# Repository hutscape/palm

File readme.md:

# Palm

> 🌴 Outdoor BLE-connected UV sensor keychain 🗝

Visit [hutscape.com/palm](https://hutscape.com/palm/) for more details.

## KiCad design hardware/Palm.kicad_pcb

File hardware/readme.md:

# Hardware

## Schematic

View the [schematic](images/schematic.pdf) and [footprint layout](images/footprint.pdf) in PDF format.

## Main components

1. nRF52 Bluefruit Feather Adafruit Breakout board
1. VEML6075 UV Index sensor Adafruit breakout board
1. RGB LED
1. LiPo

## Prototype

## Schematic

## Footprint

Front

Back

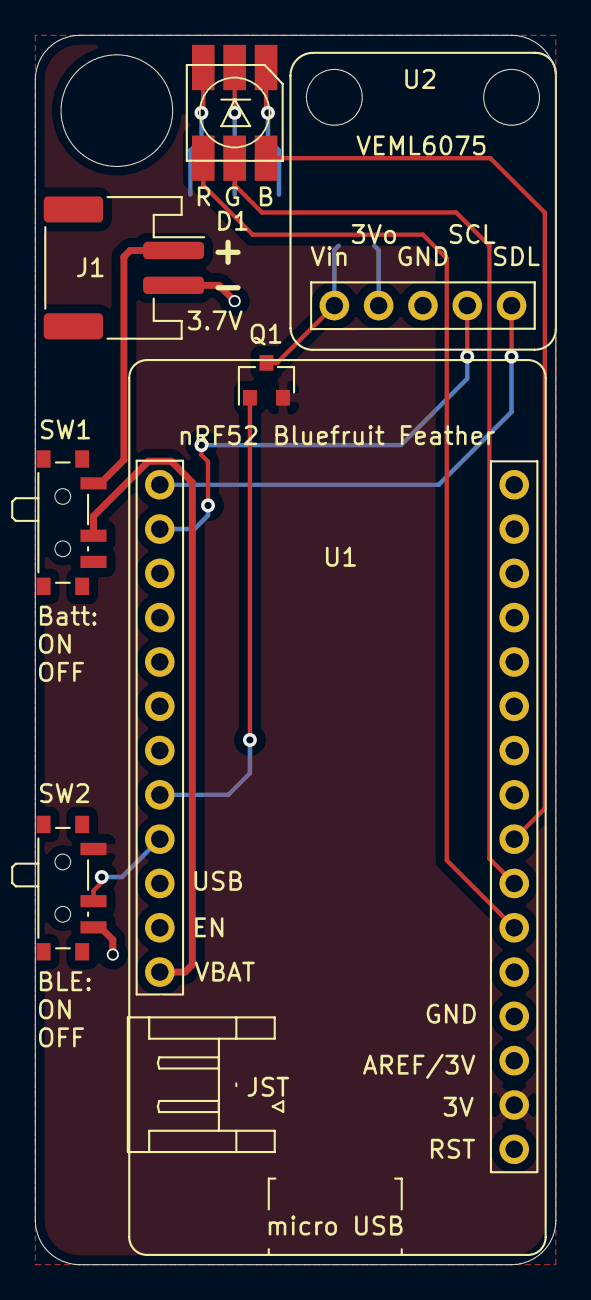
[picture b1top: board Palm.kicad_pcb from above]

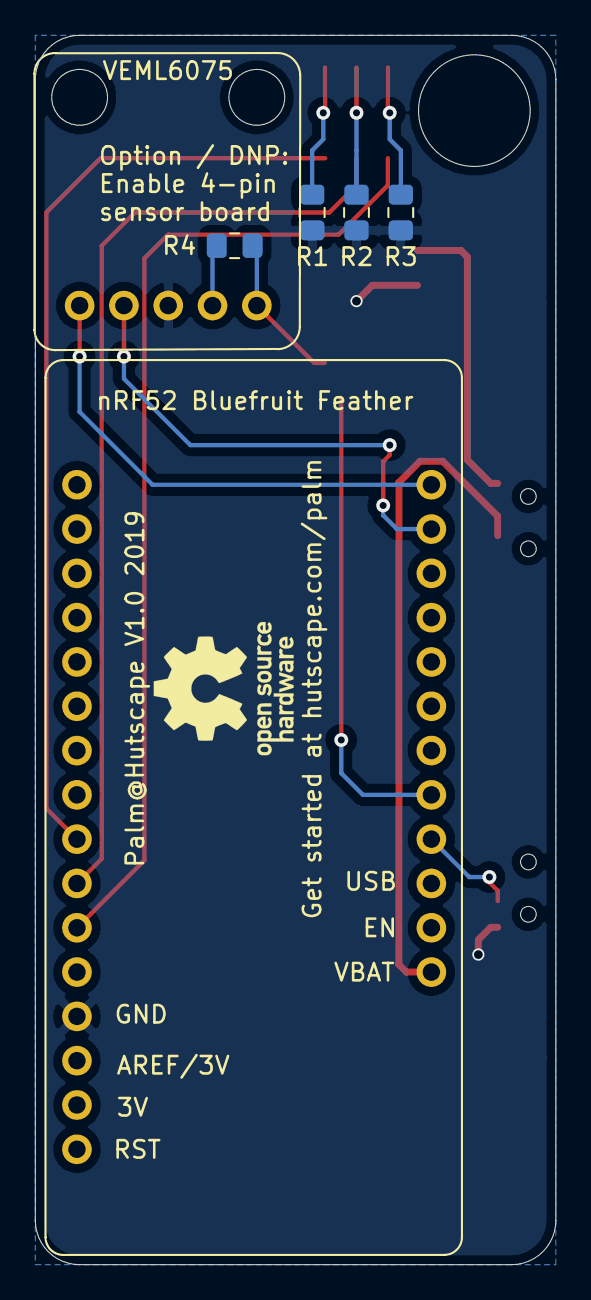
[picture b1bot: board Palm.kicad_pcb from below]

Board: 2 copper layers, 29.8 x 70.5 mm, 11 parts (4 on the bottom side), 16 nets.

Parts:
D1: LED_BARG; LED_RGB_Cree-PLCC-6_5.5x5.5mm_P2.1mm
J1: Conn_01x02_Female; JST_PH_S2B-PH-SM4-TB_1x02-1MP_P2.00mm_Horizontal
Q1: IRLML6402; SOT-23
R1, R2, R3: 1k; R_0805_2012Metric_Pad1.15x1.40mm_HandSolder
R4: 0R; R_0805_2012Metric_Pad1.15x1.40mm_HandSolder
SW1, SW2: SW_SPDT; SW_SPDT_PCM12
U1: Adafruit_nRF52_Feather; nRF52_Bluefruit_Adafruit_breakout_board
U2: VEML6075_breakout; VEML6075_breakout_board

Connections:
+3V3: Q1.2, SW2.1, U1.2
/BLUE: D1.4, U1.6
/EN_SENSOR: Q1.1, U1.24
/GREEN: D1.5, U1.7
/RED: D1.6, U1.8
/SCL: U1.18, U2.4
/SDA: U1.17, U2.5
GND: J1.2, R1.2, R2.2, R3.2, SW2.3, U1.4, U2.3
unnamed: D1.1, R1.1
unnamed: D1.2, R2.1
unnamed: D1.3, R3.1
unnamed: J1.1, SW1.1
unnamed: Q1.3, R4.1, U2.1
unnamed: R4.2, U2.2
unnamed: SW1.2, U1.28
unnamed: SW2.2, U1.25

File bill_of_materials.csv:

"Designator","Value","Q","Package","Category","Stock","Manufacturer","Manufacturer Part No. (Datasheet)","Vendor (Vendor link)","Unit cost","Total cost","Minimum Order","Description"
"D1, ","LED_BARG","1","SMD","Electronics","","Cree","=HYPERLINK(""https://docs-apac.rs-online.com/webdocs/1524/0900766b815247fa.pdf"", ""SLV6A-FKB-CK1P1G1BB7R3R3 "")","=HYPERLINK(""https://sg.rs-online.com/web/p/products/1238680/"", ""RS Components"")","0.632","6.32","10","LED_RGB: RGB LED, 6 pin package"
"J1, ","Conn_01x02_Female","1","SMD","Connector","","JST","=HYPERLINK(""https://docs-apac.rs-online.com/webdocs/13ce/0900766b813ce4bd.pdf"", ""S2B-PH-SM4-TB(LF)(SN)"")","=HYPERLINK(""https://sg.rs-online.com/web/p/products/6881353/"", ""RS Components"")","0.486","2.4299999999999997","5","Conn_01x02_Female: Generic connector, single row, 01x02, script generated (kicad-library-utils/schlib/autogen/connector/)"
"Q1, ","IRLML6402","1","SOT-23","Electronics","","Infineon","=HYPERLINK(""https://docs-apac.rs-online.com/webdocs/10c7/0900766b810c708d.pdf"", ""IRLML2246TRPBF"")","=HYPERLINK(""https://sg.rs-online.com/web/p/products/7604432/"", ""RS Components"")","0.224","1.12","5","IRLML6402: -3.7A Id, -20V Vds, P-Channel MOSFET, 65mOhm Rds, SOT-23"
"R1, R2, R3, ","1k","3","0805","Electronics","18-res-0805-1k","","","","","0","1","R_Small: Resistor, small symbol"
"R4, ","0R","1","0805","Electronics","15-res-0805-0","","","","","0","","R_Small: Resistor, small symbol"
"SW1, SW2, ","SW_SPDT","2","SMD","Connector","","","=HYPERLINK(""https://www.aliexpress.com/item/50Pcs-Mini-7-Pin-On-Off-1P2T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"", ""Link to datasheet"")","=HYPERLINK(""https://www.aliexpress.com/item/50Pcs-Mini-7-Pin-On-Off-1P2T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"", ""AliExpress"")","1.90 ","3.8","1","SW_SPDT: Switch, single pole double throw"
"U1, ","Adafruit_nRF52_Feather","1","TH","Electronics","prototype-4","Adafruit","=HYPERLINK(""https://cdn-learn.adafruit.com/assets/assets/000/052/793/ori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"", ""3406"")","=HYPERLINK(""https://www.adafruit.com/product/3406"", ""Adafruit"")","34.0","34.0","1","Adafruit_nRF52_Feather: "
"U2, ","VEML6075_breakout","1","TH","Electronics","prototype-5","Adafruit","=HYPERLINK(""https://learn.adafruit.com/assets/62587"", ""3964"")","=HYPERLINK(""https://www.adafruit.com/product/3964"", ""Adafruit"")","8.20","8.2","1","VEML6075_breakout: "
"Total:","8","11","","","","","","","","55.87","",""

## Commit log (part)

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2019-04-02 [idea] Add research on sensors, power and mcu
2019-04-02 [docs] Tweak timeline todo list
2019-04-03 [docs] Add more explaination on the use case and sensors
2019-04-03 [docs] Change sensor to Si7021
2019-04-03 [docs] Add notes on the sensor value display
2019-04-04 [docs] Fix grammar
2019-04-08 [docs] Add timeline for prototyping components lead time
2019-04-11 Add hello world code for VEML6075 UV sensor
2019-04-12 [idea] Add mechanical dimensions for main components
2019-04-12 [docs] Standardize units
2019-04-12 [prot] Add hello world code for UV sensor with nRF52 board
2019-04-12 [docs] Fix links to components
2019-04-13 [prot] Display UV values
2019-04-14 [docs] Add reference to read LiPo battery voltage
2019-04-14 [prot] Display UV sensor values with a LiPo
2019-04-15 [docs] Add main components from modules to deconstruct them
2019-04-15 [docs] Edit component parts
2019-04-16 [prot] Connect second sensor
2019-04-16 [prot] Abstract code into functions and add debug flag
2019-04-17 [prot] Use struct to read all sensor values
2019-04-17 [prot] Add comment on enabling debug mode
2019-05-09 [docs] Move component code to another repo
2019-05-09 [docs] Move datasheets to another common repo
2019-05-13 [docs] Transfer all references into a single file
2019-05-13 [docs] Synchronics structure of the project
2019-05-14 [docs] Use only UV index sensor
2019-05-23 [docs] Add library as a git submodule
2019-05-23 [docs] Calculate power consumption in advertising and transmission mode
2019-05-25 [design] Add more info about nRF52's power consumption
2019-05-25 [design] Add more notes on estimated battery life and potential batteries
2019-05-27 Add mechanical dimensions for LiPo battery
2019-05-28 [design] Add resistors to RGB LED
2019-05-28 [design] Add power tree schematic and state machine diagram
2019-05-29 [docs] Move all images to one folder
2019-05-29 [docs] Fix image path
2019-05-29 [docs] Rename in git
2019-06-02 [design] Add P-channel MOSFET switch and RGB LED
2019-06-03 [design] Update kicad library
2019-06-05 [bom] Generate bill of materials
2019-06-05 [bom] Fix generated BOM format
2019-06-05 [bom] Add more logic to creating vendor links in BOM
2019-06-05 [bom] Add category in BOM generation
2019-06-07 [footprint] Associate nRF52 breakbout board with symbol and footprint
2019-06-07 [footprint] Associate all symbols with footprint
2019-06-08 [footprint] Layout all footprints
2019-06-08 [footprint] Update footprint library
2019-06-08 [footprint] Add rats net
2019-06-09 [footprint] Add back Cu zone with GND
2019-06-09 [footprint] Link SDA/SCL and RGB LED tracks
2019-06-11 [footprint] Update footprint layout
2019-06-12 [design] Add 0ohm resistor for sensor board option
2019-06-12 [footprint] Generate gerbers
2019-06-13 [docs] Standardise gitignore
2019-06-14 [docs] Add progress on BOM and others
2019-06-15 [docs] Update hardware readme
2019-06-21 [bom] Update JST PH2 connector body orientation from straight to right angle
2019-07-02 [test] Add initial test for RGB LED colors on OCB integration
2019-07-02 [test] Add test for enabling, connecting and reading UV sensor
2019-07-02 [test] Add a todo task to disable sensor from pin
2019-07-03 [test] Measure UV Index in a loop and display LED color
2019-07-04 [test] Turn off and on the MOSFET with delays
2019-07-04 [test] Complete 14 tests with BLE
2019-07-04 [si] Final firmware on PCB
2019-07-05 [docs] Complete schedule
2019-07-08 [docs] Use imperative verbs for bullets
2019-07-10 [design] Remove red LED toggling
2019-07-16 [docs] Add jekyll
2019-07-16 [docs] Add optional includes
2019-07-16 [docs] Style getting started page
2019-07-16 [docs] Style software page
2019-07-16 [docs] Add BOM
2019-07-16 [docs] Add references page
2019-07-16 [docs] Style lessons page
2019-07-16 [docs] Style power page
2019-07-16 [docs] Design schedule page
2019-07-17 Add GA
2019-07-17 [docs] Amend schedule to month view
2019-07-18 [docs] Test git submodule for _includes folder
2019-07-18 [docs] Add prototype images
2019-07-18 [docs] Add header tags
2019-07-18 [docs] Simplify readme
2019-07-19 [docs] Remove BOM columns
2019-07-21 [docs] Update BOM column
2019-07-22 [docs] Fix code styling
2019-07-22 [docs] Add license
2019-07-22 [docs] Add BOM layout code in a common submodule
2019-07-22 [docs] Use common hardware layout
2019-07-22 [docs] Add starter images from submodule
2019-07-22 [docs] Use lessons learnt from template
2019-07-22 [docs] Add schedule layout
2019-07-22 [docs] Add software as a layout and content
2019-07-22 [docs] Add lessons data inside page
2019-07-22 [docs] Take schedule data form page
2019-07-22 [docs] Use protocol relative URLs
2019-07-23 [docs] Add completion date
2019-07-23 [design] Add battery level code in firmware
2019-07-23 [design] Display GATT Service and characteristics for battery level
2019-07-23 [docs] Add note on editing
2019-07-24 [docs] Add v2.0 subtitle
2019-07-24 [docs] Fix BOM
2019-07-24 [docs] changed breadth to width
2019-07-24 [docs] Add status if ongoing
2019-07-25 [docs] Update git submodule
2019-07-25 [docs] Add iBom
2019-07-25 [docs] Update git submodule with credits in header
2019-07-25 [docs] Remove auto generated scrollbar CSS in iBom
2019-07-29 [docs] Add 5 days for battery life
2019-07-30 [docs] Update git submodules
2019-07-30 [docs] Add QSun as a reference
2019-08-01 [docs] Overflow-x for table view in mobile
2019-08-01 [docs] Add space in BOM vendors
2019-08-01 [docs] Hide iBOM on touch devices
2019-08-02 [design] Initiate Web BLE connection to read UV
2019-08-02 Duplicate functions for 2 GATT services
2019-08-02 Combine all functions
2019-08-02 Change background color according to UV Index
2019-08-02 Publish Web BLE as site
2019-08-02 [docs] Amend code link
2019-08-02 [docs] Sync design page
2019-08-04 [docs] Add currency conversion
2019-08-05 [docs] Add notes on lessons learnt
2019-08-07 [software] Add filter for detecting BLE device prefix name
2019-08-07 [docs] Add user stories
2019-08-07 [docs] Add version to title
2019-08-15 [docs] Clean up Makefile
2019-08-16 [docs] Update common kicad library
2019-08-17 [docs] Update submodule with header links
2019-08-17 [docs] Add fixed navbar
2019-08-21 [docs] Add BOM iterator
2019-09-05 [docs] Generate BOM info automatically
2019-09-05 [docs] Add git secrets
2019-09-05 [docs] Add scripts folder as a git submodule
2019-09-09 [docs] Move power tree schematic to under power page
2019-09-12 [docs] Setup github action for jekyll
2019-09-16 [docs] Update submodules and gems
2019-09-16 [docs] Add icons
2019-09-16 [docs] Remove github actions for failing jekyll with submodule
2019-09-18 [docs] Move power diagrams to power folder
2019-09-18 [docs] Add mechanical details as yml
2019-09-19 [docs] Improve BOM page
2019-10-08 [design] Fix and upgrade firmware dependancies
2019-10-09 ci: add ci for jekyll
2019-10-11 fix: change unit cost from string to float for proper sorting
2019-10-12 feat: tweak BOM column header and serial column
2019-10-13 feat: add external link icon beside a vendor link
2019-10-28 feat: add download buttons on start page
2019-10-28 feat: add button link for gerber files
2019-11-07 feat: add notes for BOM column
2019-11-11 chore: update git submodules for scripts and bom
2019-11-18 chore: update submodules with global and project specific symbols and footprints
2019-12-03 refactor: change navbar components to tutorials
2020-08-11 refactor: update dependancies
2021-03-18 feat: add privacy info for hw apis on web
2021-03-20 refactor: improve info on using Web BLE
2021-03-29 Bump kramdown from 2.3.0 to 2.3.1
    Bumps [kramdown](https://github.com/gettalong/kramdown) from 2.3.0 to 2.3.1.
    - [Release notes](https://github.com/gettalong/kramdown/releases)
    - [Changelog](https://github.com/gettalong/kramdown/blob/master/doc/news.page)
    - [Commits](https://github.com/gettalong/kramdown/commits)
2021-04-30 Bump rexml from 3.2.4 to 3.2.5
    Bumps [rexml](https://github.com/ruby/rexml) from 3.2.4 to 3.2.5.
    - [Release notes](https://github.com/ruby/rexml/releases)
    - [Changelog](https://github.com/ruby/rexml/blob/master/NEWS.md)
    - [Commits](https://github.com/ruby/rexml/compare/v3.2.4...v3.2.5)
2021-05-06 chore: update dependancies
2021-06-27 chore: fix build failing
2021-06-27 chore: remove unused gem
2021-06-28 refactor: remove google analytics
2021-07-13 Bump addressable from 2.7.0 to 2.8.0
    Bumps [addressable](https://github.com/sporkmonger/addressable) from 2.7.0 to 2.8.0.
    - [Release notes](https://github.com/sporkmonger/addressable/releases)
    - [Changelog](https://github.com/sporkmonger/addressable/blob/main/CHANGELOG.md)
    - [Commits](https://github.com/sporkmonger/addressable/compare/addressable-2.7.0...addressable-2.8.0)
    ---
    updated-dependencies:
2021-07-15 chore: update addressable dependancy
2021-08-10 chore: update year in license
2021-08-10 fix: remove fixed top navbar
2021-08-23 refactor: combine lessons, references and schedule pages into others
2021-08-26 chore: update submodule
2021-08-26 refator: seperate layouts and includes as submodules
2021-09-10 fix: reset fonts after inserting iBom
2021-10-05 fix: add back content on layout pages
2021-10-07 fix: add example page content in layouts
2021-10-20 docs: reword prequisites to simpler and similar
2021-10-23 chore: update files
2021-12-17 refactor: change styling for dependancies, pre-requisites, and components
2022-01-08 refactor: organize power section
2022-03-09 feat: add favicons to project head
2022-03-09 chore: update anchor.js from 4.2.0 to 4.3.1
2022-03-09 chore: update bulma.css from 0.9.2 to 0.9.3
2022-03-18 chore: update rubygems on Monterey
2022-04-13 "feat: add monthly progress in scehdule"
2022-04-13 refactor: remove _data/project.json and combine into _config.yml
2022-04-20 refactor: make a parent data node for download buttons
2022-04-20 "refactor: sync status tags and update footer"
2022-04-20 "refactor: sync status tags for ongoing"
2022-04-20 "refactor: seperate code into more partials"
2022-04-21 refactor: remove gerber_url to link to GitHub releases page
2022-04-21 "refactor: seperate BOM page into more partials"
2022-04-21 "refactor: seperate Design page into more partials"
2022-04-22 "refactor: seperate Example page into more partials"
2022-05-13 feat: update text editor and FreeCAD files in gitignore
2022-05-18 "feat: add 18650 battery 3D model to KiCad library"
2022-05-19 "feat: add /case layout for projects with enclosure designs"
2022-05-19 "refactor: improve FreeCAD file name and link"
2022-07-21 refactor: rename hardware layout to pcb
2022-07-21 refactor: rename examples to code
2022-07-21 "fix: change link to code images"
2022-07-22 fix: add only demo firmware link on start page
2022-07-22 "fix: change GitHub URL for HTML code examples"
2022-07-22 chore: move images from hardware to pcb directory
2022-07-25 feat: `detect demo code
2023-12-15 chore: update gitsubmodules
2024-02-26 chore: update submodule for manufacturing params
2024-02-29 chore: update submodule to fix image url display for relative project paths
2024-02-29 chore: update submodules to seperate /case page into sections
2024-03-04 feat: display all prototype images until defined max_prototype_images
2024-03-13 chore: update submodules to display cost breakdown section
2024-03-17 chore: update submodules to display cost and schedule on /others
2024-03-27 refactor: divide others page into csq and resources
2024-03-29 chore: update submodules to remove unused Others page
2024-04-01 chore: update submodules to hyperlink images
2024-04-01 chore: update submodules to display manufactured PCBs
2024-04-11 docs (power): remove HTML and convert content to only markdown
2024-04-12 chore: update submodules to upgrade to latest JS and CSS libraries
2024-04-12 refactor: simplify putting content on start page with only Markdown
2024-05-04 chore: update submodules to add a link to download demo code
2024-05-04 fix: update to fix broken link to demo code
2024-05-06 chore: update submodules to remove unused link to software downloads
2024-05-06 refactor (docs): simplify iteration ideas into one big list
2024-10-11 chore: update submodule to add checkboxes to Feature list
2024-11-08 docs: update navbar
2024-11-13 docs: add project name reasoning
2024-11-14 chore: update submodule to conditionally display edit button
